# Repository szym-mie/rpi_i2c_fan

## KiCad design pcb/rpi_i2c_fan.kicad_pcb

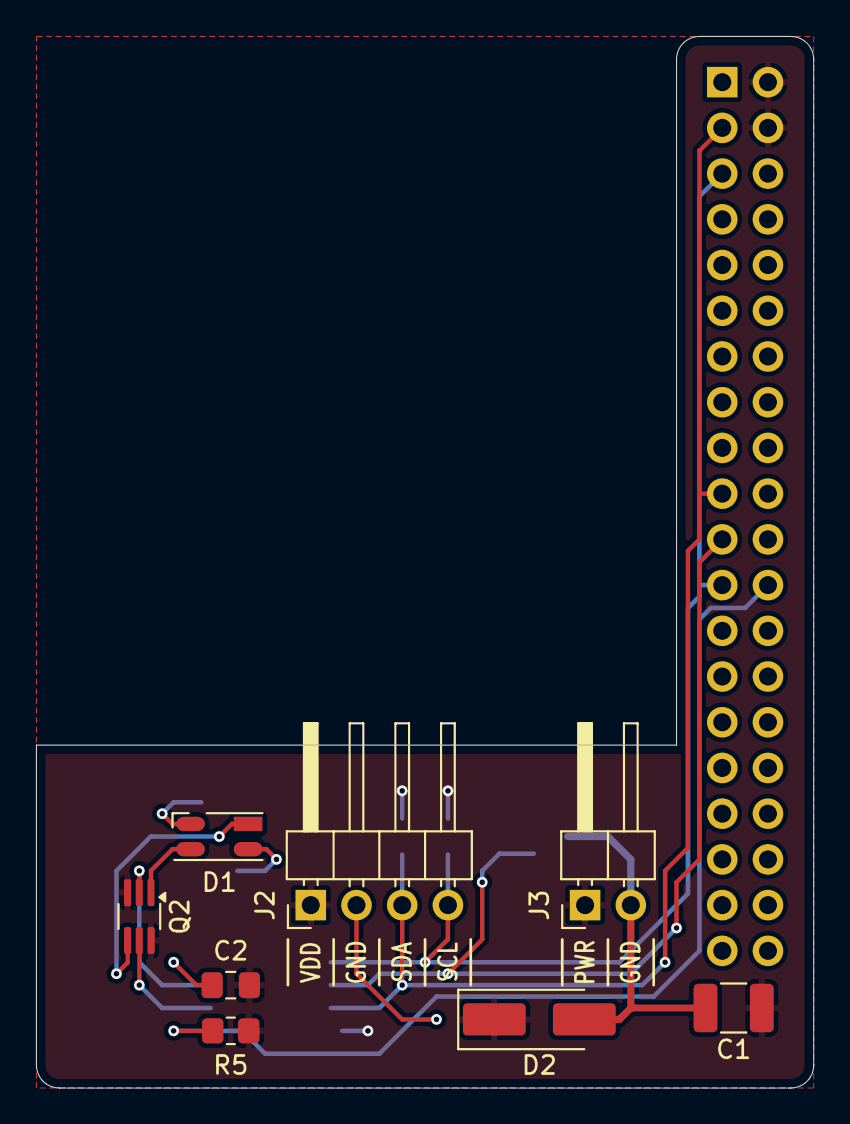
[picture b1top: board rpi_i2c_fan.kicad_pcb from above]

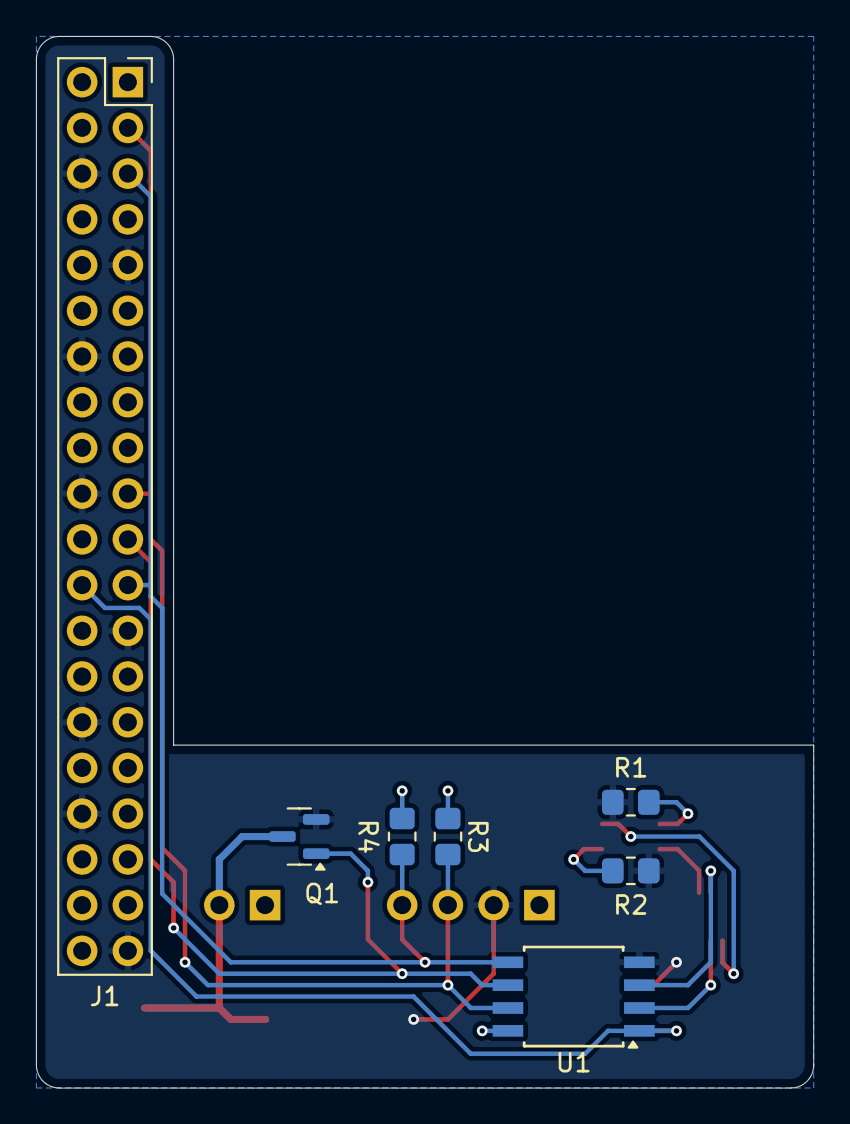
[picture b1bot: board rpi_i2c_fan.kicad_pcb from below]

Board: 2 copper layers, 43.2 x 58.4 mm, 15 parts (7 on the bottom side), 13 nets.

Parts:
C1: 100u; C_1210_3225Metric_Pad1.33x2.70mm_HandSolder
C2: 1u; C_0805_2012Metric_Pad1.18x1.45mm_HandSolder
D1: KPTB-1612; LED_Kingbright_KPBD-3224
D2: SK34; D_SMA_Handsoldering
J1: RPI_INOUT; PinSocket_2x20_P2.54mm_Vertical
J2: DPY_OUT; PinHeader_1x04_P2.54mm_Horizontal
J3: FAN_OUT; PinHeader_1x02_P2.54mm_Horizontal
Q1: IRLML6346; SOT-23
Q2: 2N7002PS; SOT-363_SC-70-6_Handsoldering
R1: 200; R_0805_2012Metric_Pad1.20x1.40mm_HandSolder
R2: 120; R_0805_2012Metric_Pad1.20x1.40mm_HandSolder
R3, R4: 4k7; R_0805_2012Metric_Pad1.20x1.40mm_HandSolder
R5: 10k; R_0805_2012Metric_Pad1.20x1.40mm_HandSolder
U1: ATtiny85-20S; SOIC-8W_5.3x5.3mm_P1.27mm

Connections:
5V0: C1.1, C2.1, D2.1 (K), J1.2 (5V), J1.4 (5V), J2.1, J3.1, Q2.3 (D), Q2.6 (D), R3.1, R4.1, R5.2, U1.8 (VCC)
/BUS.CK: J1.5 (SCL/GPIO3), J1.23 (SCLK0/GPIO11), J2.4, R4.2, U1.5 (AREF/PB0)
/BUS.DI: J1.21 (MISO0/GPIO9), Q1.1 (G), U1.6 (PB1)
/BUS.DO: J1.3 (SDA/GPIO2), J1.19 (MOSI0/GPIO10), J2.3, R3.2, U1.7 (PB2)
/BUS.RES: J1.24 (~CE0/GPIO8), R5.1, U1.1 (~RESET/PB5)
/LED.G: Q2.2 (G), U1.3 (XTAL2/PB4)
/LED.R: Q2.5 (G), U1.2 (XTAL1/PB3)
GND: C2.2, J1.6 (GND), J1.9 (GND), J1.14 (GND), J1.20 (GND), J1.25 (GND), J1.30 (GND), J1.34 (GND), J1.39 (GND), J2.2, Q1.2 (S), R1.2, R2.2, U1.4 (GND)
unnamed: D1.1 (A1), Q2.4 (S)
unnamed: D1.4 (A2), Q2.1 (S)
unnamed: D1.2 (K1), R1.1
unnamed: D1.3 (K2), R2.1
unnamed: C1.2, D2.2 (A), J3.2, Q1.3 (D)

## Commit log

2024-08-12 initial testing
